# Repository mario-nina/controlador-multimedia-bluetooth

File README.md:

# Controlador Multimedia Bluetooth

Controlador multimedia inalámbrico portátil basado en ESP32 que permite gestionar la reproducción de audio en una computadora mediante comunicación Bluetooth.

---

## Tabla de contenidos

- [Descripción](#descripción)
- [Características](#características)
- [Requisitos](#requisitos)
- [Instalación](#instalación)
- [Uso](#uso)
- [Estructura del proyecto](#estructura-del-proyecto)
- [Hardware](#hardware)
- [Firmware](#firmware)
- [Documentación](#documentación)
- [Versionado](#versionado)
- [Licencia](#licencia)
- [Autor](#autor)

---

## Descripción

El sistema permite controlar remotamente la reproducción multimedia de una laptop sin requerir interacción física directa con la misma. Comunica mediante protocolo Bluetooth HID, lo que garantiza compatibilidad nativa con el sistema operativo sin necesidad de software adicional.

Desarrollado como proyecto de la materia Sistemas Embebidos II de la carrera de Ingeniería Mecatrónica en la Universidad Católica Boliviana.

---

## Características

- Control de reproducción: Play/Pause
- Navegación entre pistas: Siguiente y Anterior
- Control de volumen: Incremento y Decremento
- Silenciamiento: Mute/Unmute
- Comunicación inalámbrica mediante Bluetooth HID
- Operación autónoma mediante batería Li-ion recargable
- Indicadores visuales de estado de conexión y batería
- Gestión energética con modem sleep y escalado dinámico de frecuencia CPU

---

## Requisitos

### Hardware

| Componente | Especificación |
|------------|----------------|
| Microcontrolador | ESP32 WROOM-32 (DevKit 30 pines) |
| Batería | Li-ion 18650 3.7V 2600mAh |
| Módulo de carga | TP4056 USB-C con protección |
| Boost converter | MT3608 |
| Regulador | AMS1117-3.3V |
| Encoder rotativo | Alps EC11 |
| Botones | 3 pulsadores táctiles |
| Indicadores | LED azul (Bluetooth — GPIO32), LED rojo (batería — GPIO33) |

### Software

| Herramienta | Versión |
|-------------|---------|
| ESP-IDF | v6.0.1 |
| KiCad | 8.0 |
| Sistema operativo | Ubuntu 24.04 LTS |
| Compilador | xtensa-esp-elf-gcc 15.2.0 |
| Python | 3.12.3 |
| CMake | 3.28.3 |
| Git | 2.43.0 |

---

## Instalación

### Configuración del entorno

1. Instalar ESP-IDF v6.0.1 siguiendo la [documentación oficial](https://docs.espressif.com/projects/esp-idf/en/stable/esp32/get-started/index.html).

2. Clonar el repositorio:
```bash
git clone git@github.com:mario-nina/controlador-multimedia-bluetooth.git
cd controlador-multimedia-bluetooth
```

3. Activar el entorno ESP-IDF:
```bash
get_idf
```

4. Configurar el chip objetivo:
```bash
cd firmware
idf.py set-target esp32
```

5. Compilar el firmware:
```bash
idf.py build
```

6. Flashear el ESP32:
```bash
idf.py flash monitor
```

---

## Uso

1. Encender el dispositivo.
2. En la laptop, activar Bluetooth y buscar dispositivos disponibles.
3. Emparejar con el dispositivo **"Controlador Multimedia"**.
4. Una vez conectado, usar los controles:

| Control | Función |
|---------|---------|
| Encoder — girar derecha | Subir volumen |
| Encoder — girar izquierda | Bajar volumen |
| Encoder — presionar | Play/Pause |
| Botón 1 | Siguiente pista |
| Botón 2 | Pista anterior |
| Botón 3 | Mute/Unmute |

### Indicadores visuales

| LED | Estado | Significado |
|-----|--------|-------------|
| Azul | Parpadeo rápido | Sin conexión BLE — advertising |
| Azul | Apagado | Conexión BLE activa |
| Rojo | Apagado | Batería OK (>= 3400mV) |
| Rojo | Parpadeo lento | Batería baja (< 3400mV) |
| Rojo | Parpadeo rápido | Batería crítica (< 3200mV) |

---

## Estructura del proyecto
controlador-multimedia-bluetooth/
├── firmware/                          # Código fuente del firmware (ESP-IDF)
│   ├── main/                          # Punto de entrada de la aplicación
│   │   └── firmware.c
│   └── components/                    # Módulos independientes
│       ├── common/                    # Configuración global del sistema
│       │   └── include/
│       │       ├── config.h           # Constantes de configuración del sistema
│       │       └── pines.h            # Mapa de asignación de pines GPIO
│       ├── comunicacion_bt/           # Stack NimBLE + perfil HID Consumer Control
│       ├── control_leds/              # Patrones de LEDs via esp_timer
│       ├── driver_entrada/            # Botones (ISR) + encoder rotativo (PCNT)
│       └── gestion_energia/           # Monitoreo ADC batería + modem sleep
├── hardware/                          # Archivos de diseño de hardware
│   ├── kicad/                         # Proyecto KiCad (esquemático + PCB)
│   ├── exportaciones/                 # Archivos exportados desde KiCad
│   │   ├── esquematico/               # PDF y SVG del esquemático
│   │   ├── gerbers/                   # Archivos Gerber para fabricación
│   │   └── step/                      # Modelos 3D de la carcasa
│   └── pines.md                       # Asignación de pines con justificación técnica
├── docs/                              # Documentación técnica
│   ├── memoria_tecnica/               # Memoria técnica del proyecto (entrega académica)
│   ├── diseno_pcb.md                  # Decisiones de diseño PCB con justificación
│   ├── manual_usuario/                # Manual de usuario
│   └── lista_materiales/             # Lista de materiales con especificaciones y costos
├── test/                              # Pruebas y validación
│   └── resultados/                    # Resultados de pruebas documentadas
├── CHANGELOG.md
├── CONTRIBUTING.md
├── CONVENTIONS.md
├── LICENSE
├── ROADMAP.md
└── README.md

---

## Hardware

El sistema se compone de cuatro subsistemas principales:

- **Interfaz de usuario** — encoder rotativo Alps EC11 y tres botones táctiles para generación de comandos
- **Microcontrolador** — ESP32 WROOM-32 como unidad central de procesamiento
- **Sistema de alimentación** — batería Li-ion 18650 → TP4056 (carga USB-C) → MT3608 (boost) → AMS1117-3.3V
- **Indicadores de estado** — LED azul (GPIO32) para Bluetooth y LED rojo (GPIO33) para batería

Los archivos de diseño se encuentran en `hardware/kicad/` y las exportaciones en `hardware/exportaciones/`.

---

## Firmware

Desarrollado en C mediante ESP-IDF v6.0.1 con arquitectura basada en FreeRTOS.

Separación de responsabilidades en componentes independientes:

| Componente | Responsabilidad |
|------------|-----------------|
| `common` | Configuración global — `config.h` y `pines.h` |
| `driver_entrada` | Lectura de botones (ISR + debounce) y encoder (PCNT) |
| `comunicacion_bt` | Stack NimBLE, advertising, perfil HID Consumer Control |
| `control_leds` | Patrones de iluminación via esp_timer |
| `gestion_energia` | Monitoreo ADC batería y modem sleep via esp_pm |

---

## Documentación

| Documento | Ubicación | Descripción |
|-----------|-----------|-------------|
| Asignación de pines | `hardware/pines.md` | Pines GPIO con justificación técnica y restricciones del ESP32 |
| Decisiones de diseño PCB | `docs/diseno_pcb.md` | Criterios técnicos aplicados en el diseño del PCB |
| Memoria técnica | `docs/memoria_tecnica/` | Documento académico de descripción del proyecto |
| Historial de cambios | `CHANGELOG.md` | Registro de cambios por versión |
| Roadmap | `ROADMAP.md` | Estado actual y tareas pendientes por área |

---

## Versionado

Este proyecto usa [SemVer](https://semver.org/lang/es/) para el versionado.
El historial de cambios se documenta en [CHANGELOG.md](CHANGELOG.md).

---

## Licencia

Este proyecto está bajo la licencia MIT. Ver [LICENSE](LICENSE) para más detalles.

---

## Autor

**Mario Nina**
Ingeniería Mecatrónica — Universidad Católica Boliviana
GitHub: [@mario-nina](https://github.com/mario-nina)

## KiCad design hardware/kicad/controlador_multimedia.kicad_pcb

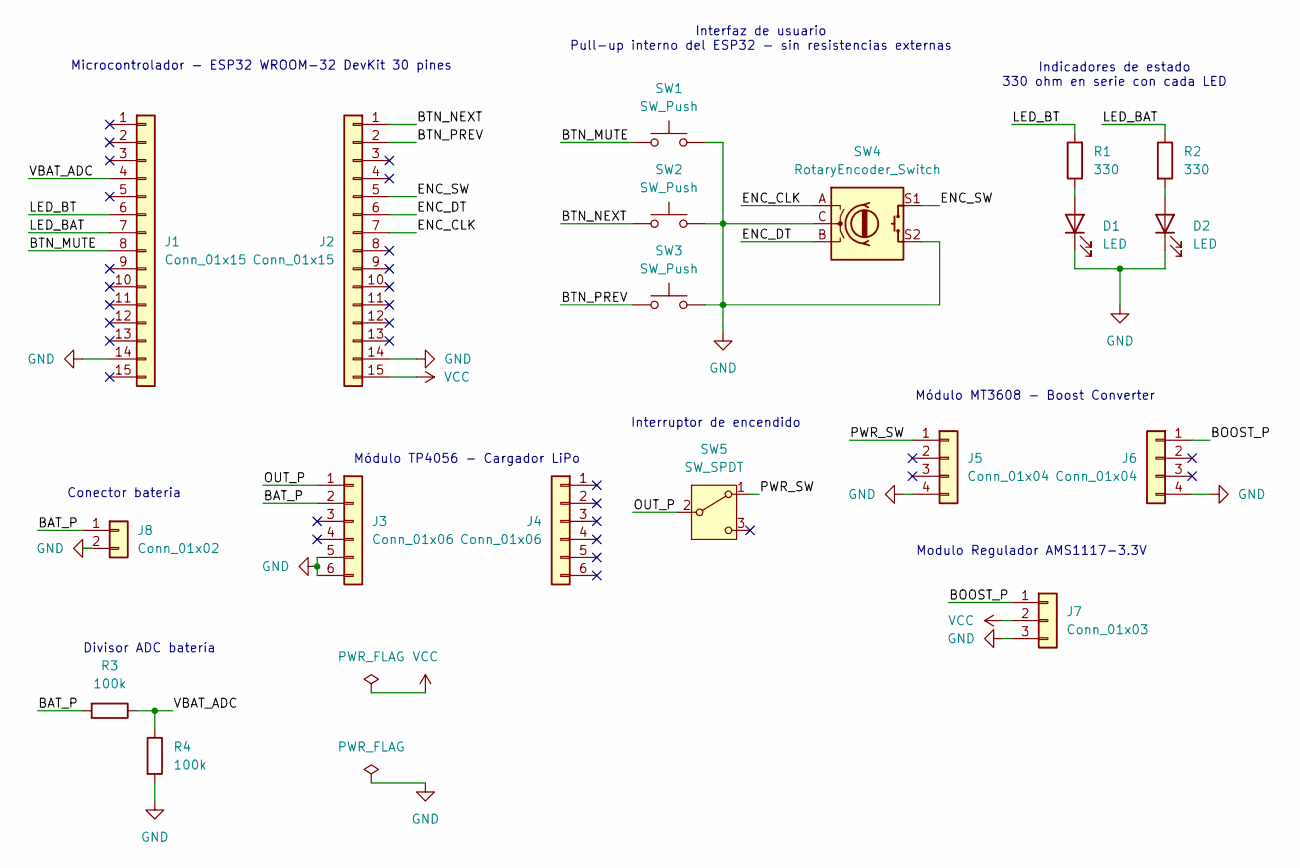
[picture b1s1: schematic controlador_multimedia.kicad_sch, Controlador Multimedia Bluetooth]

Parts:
D1, D2: LED; LED_D5.0mm
J1, J2: Conn_01x15; PinSocket_1x15_P2.54mm_Vertical
J3, J4: Conn_01x06; PinHeader_1x06_P2.54mm_Vertical
J5, J6: Conn_01x04; PinHeader_1x04_P2.54mm_Vertical
J7: Conn_01x03; PinHeader_1x03_P2.54mm_Vertical
J8: Conn_01x02; TerminalBlock_Phoenix_MKDS-1,5-2_1x02_P5.00mm_Horizontal
R1, R2: 330; R_Axial_DIN0207_L6.3mm_D2.5mm_P7.62mm_Horizontal
R3, R4: 100k; R_Axial_DIN0207_L6.3mm_D2.5mm_P7.62mm_Horizontal
SW1, SW2, SW3: SW_Push; SW_PUSH_6mm_H5mm
SW4: RotaryEncoder_Switch; RotaryEncoder_Alps_EC11E-Switch_Vertical_H20mm
SW5: SW_SPDT; Schiebeschalter_SS-12D00

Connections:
/BAT_P: J3.2, J8.1, R3.2
/BOOST_P: J6.1, J7.1
/BTN_MUTE: J1.8, SW1.1
/BTN_NEXT: J2.1, SW2.1
/BTN_PREV: J2.2, SW3.1
/ENC_CLK: J2.7, SW4.A
/ENC_DT: J2.6, SW4.B
/ENC_SW: J2.5, SW4.S1
/LED_BAT: J1.7, R2.1
/LED_BT: J1.6, R1.2
/OUT_P: J3.1, SW5.2 (B)
/PWR_SW: J5.1, SW5.1 (A)
/VBAT_ADC: J1.4, R3.1, R4.1
GND: D1.1 (K), D2.1 (K), J1.14, J2.14, J3.5, J3.6, J5.4, J6.4, J7.3, J8.2, R4.2, SW1.2, SW2.2, SW3.2, SW4.C, SW4.S2
unnamed: D1.2 (A), R1.1
unnamed: D2.2 (A), R2.2
VCC: J2.15, J7.2

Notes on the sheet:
Módulo TP4056 - Cargador LiPo
Módulo MT3608 - Boost Converter
Interfaz de usuario Pull-up interno del ESP32 - sin resistencias externas
Indicadores de estado 330 ohm en serie con cada LED
Microcontrolador - ESP32 WROOM-32 DevKit 30 pines
Divisor ADC batería
Conector bateria
Modulo Regulador AMS1117-3.3V
Interruptor de encendido

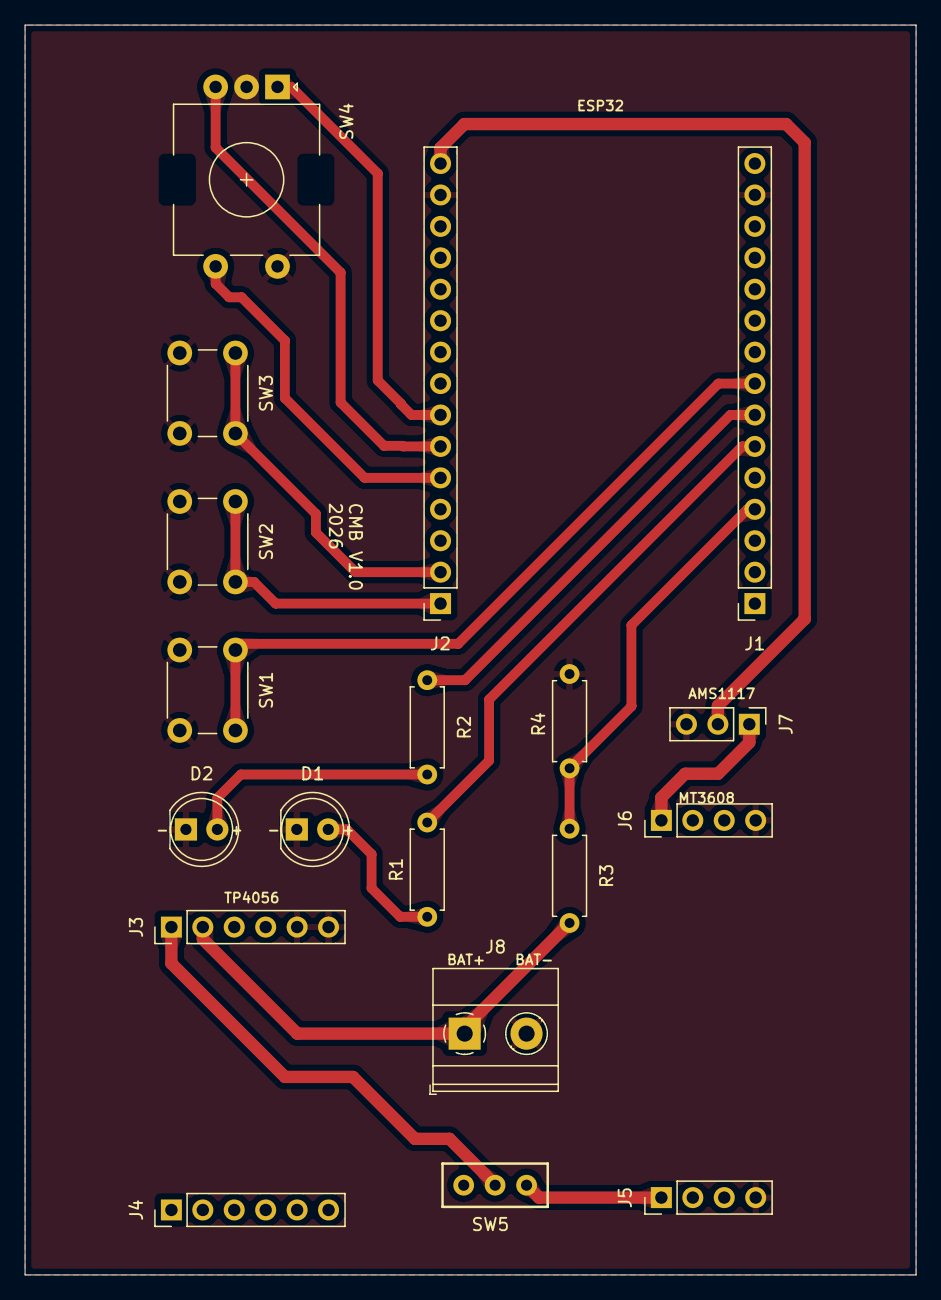
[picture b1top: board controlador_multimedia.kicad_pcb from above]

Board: 2 copper layers, 72.0 x 101.0 mm, 19 parts (0 on the bottom side), 17 nets.

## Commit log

2026-05-16 chore: estructura inicial del repositorio
2026-05-17 feat: crear proyecto ESP-IDF con target esp32
2026-05-17 chore: excluir archivos del IDE Espressif del repositorio
2026-05-17 test: confirmar blink GPIO26 en hardware físico
2026-05-17 hardware: iniciar esquemático con headers ESP32 DevKit
2026-05-17 chore: excluir archivos temporales de KiCad del repositorio
2026-05-17 docs: agregar versiones del entorno de desarrollo
2026-05-17 feat: crear estructura de 4 componentes ESP-IDF
2026-05-17 chore: registrar carpeta de componentes en CMakeLists raíz
2026-05-17 docs: agregar tabla de pines y roadmap del proyecto
2026-05-17 feat: implementar control_leds con patrones via esp_timer
2026-05-17 test: confirmar GPIO26 y GPIO27 en hardware físico
2026-05-17 test: confirmar GPIO22 GPIO23 GPIO25 sin rebotes en hardware
2026-05-17 feat: implementar driver_entrada con botones e interrupciones GPIO
2026-05-17 feat: separar driver_entrada en botones.c y encoder.c con PCNT
2026-05-17 feat: implementar máquina de estados y tareas input_task y command_task
2026-05-17 docs: agregar pines.md con asignación completa y restricciones del ESP32
2026-05-17 hardware: agregar botones, encoder y net labels al esquemático KiCad
2026-05-17 chore: eliminar archivo de autoguardado de KiCad
2026-05-17 chore: agregar archivo de autoguardado de KiCad a gitignore
2026-05-17 chore: agregar sdkconfig.defaults con configuración NimBLE
2026-05-17 feat: implementar stack NimBLE con advertising y callbacks de conexión
2026-05-18 feat: implementar perfil HID Consumer Control con reportes BLE
2026-05-30 feat: agregar Device Information Service y control de suscripcion HID
2026-05-30 test: registrar resultados de pruebas de integración Fase 9
2026-05-30 hardware: completar esquemático con cadena de potencia y ERC sin errores
2026-05-31 hardware: asignar huellas y modelos 3D a todos los componentes
2026-05-31 chore: reestructurar repositorio
2026-05-31 fix: corregir workflow CI para usar esp-idf-ci-action oficial
2026-05-31 refactor: centralizar pines en common/pines.h
2026-05-31 feat: implementar gestion_energia con ADC batería y power_task
2026-05-31 feat: integrar LEDs con estado BT y nivel batería
2026-05-31 refactor: auditoría de código — limpieza general
2026-05-31 feat: implementar modem sleep mediante esp_pm para reducir consumo BLE
2026-06-01 refactor: reorganizar arquitectura — config.h, buenas prácticas y limpieza general
2026-06-02 hardware: agregar diseño PCB v1.0 con ruteo completo, plano GND y Gerbers
2026-06-07 hardware: reasignar LEDs GPIO26/27 → GPIO32/33 para facilitar ruteo PCB
2026-06-07 hardware: reestructurar carpetas — kicad/ y exportaciones/
2026-06-07 docs: agregar decisiones de diseño PCB v1.0
2026-06-07 docs: reestructurar roadmap por áreas de trabajo
2026-06-07 docs: actualizar CHANGELOG — corregir inconsistencias y agregar v0.2.0
2026-06-07 docs: actualizar README — hardware, estructura y firmware actualizados
2026-06-07 test: renombrar y actualizar resultados de integración completa
2026-06-07 docs: agregar lista de materiales con precios a junio 2026
2026-06-07 docs: agregar manual de usuario v1.0
2026-06-07 docs: corregir manual de usuario
2026-06-07 docs: corregir disposición de controles en manual de usuario
2026-06-07 test: agregar protocolo de pruebas formales
2026-06-07 docs: actualizar roadmap — PCB completa, manual y lista de materiales
2026-06-07 docs: agregar entrada v0.3.0 al CHANGELOG
2026-06-08 docs: agregar informe técnico del proyecto
